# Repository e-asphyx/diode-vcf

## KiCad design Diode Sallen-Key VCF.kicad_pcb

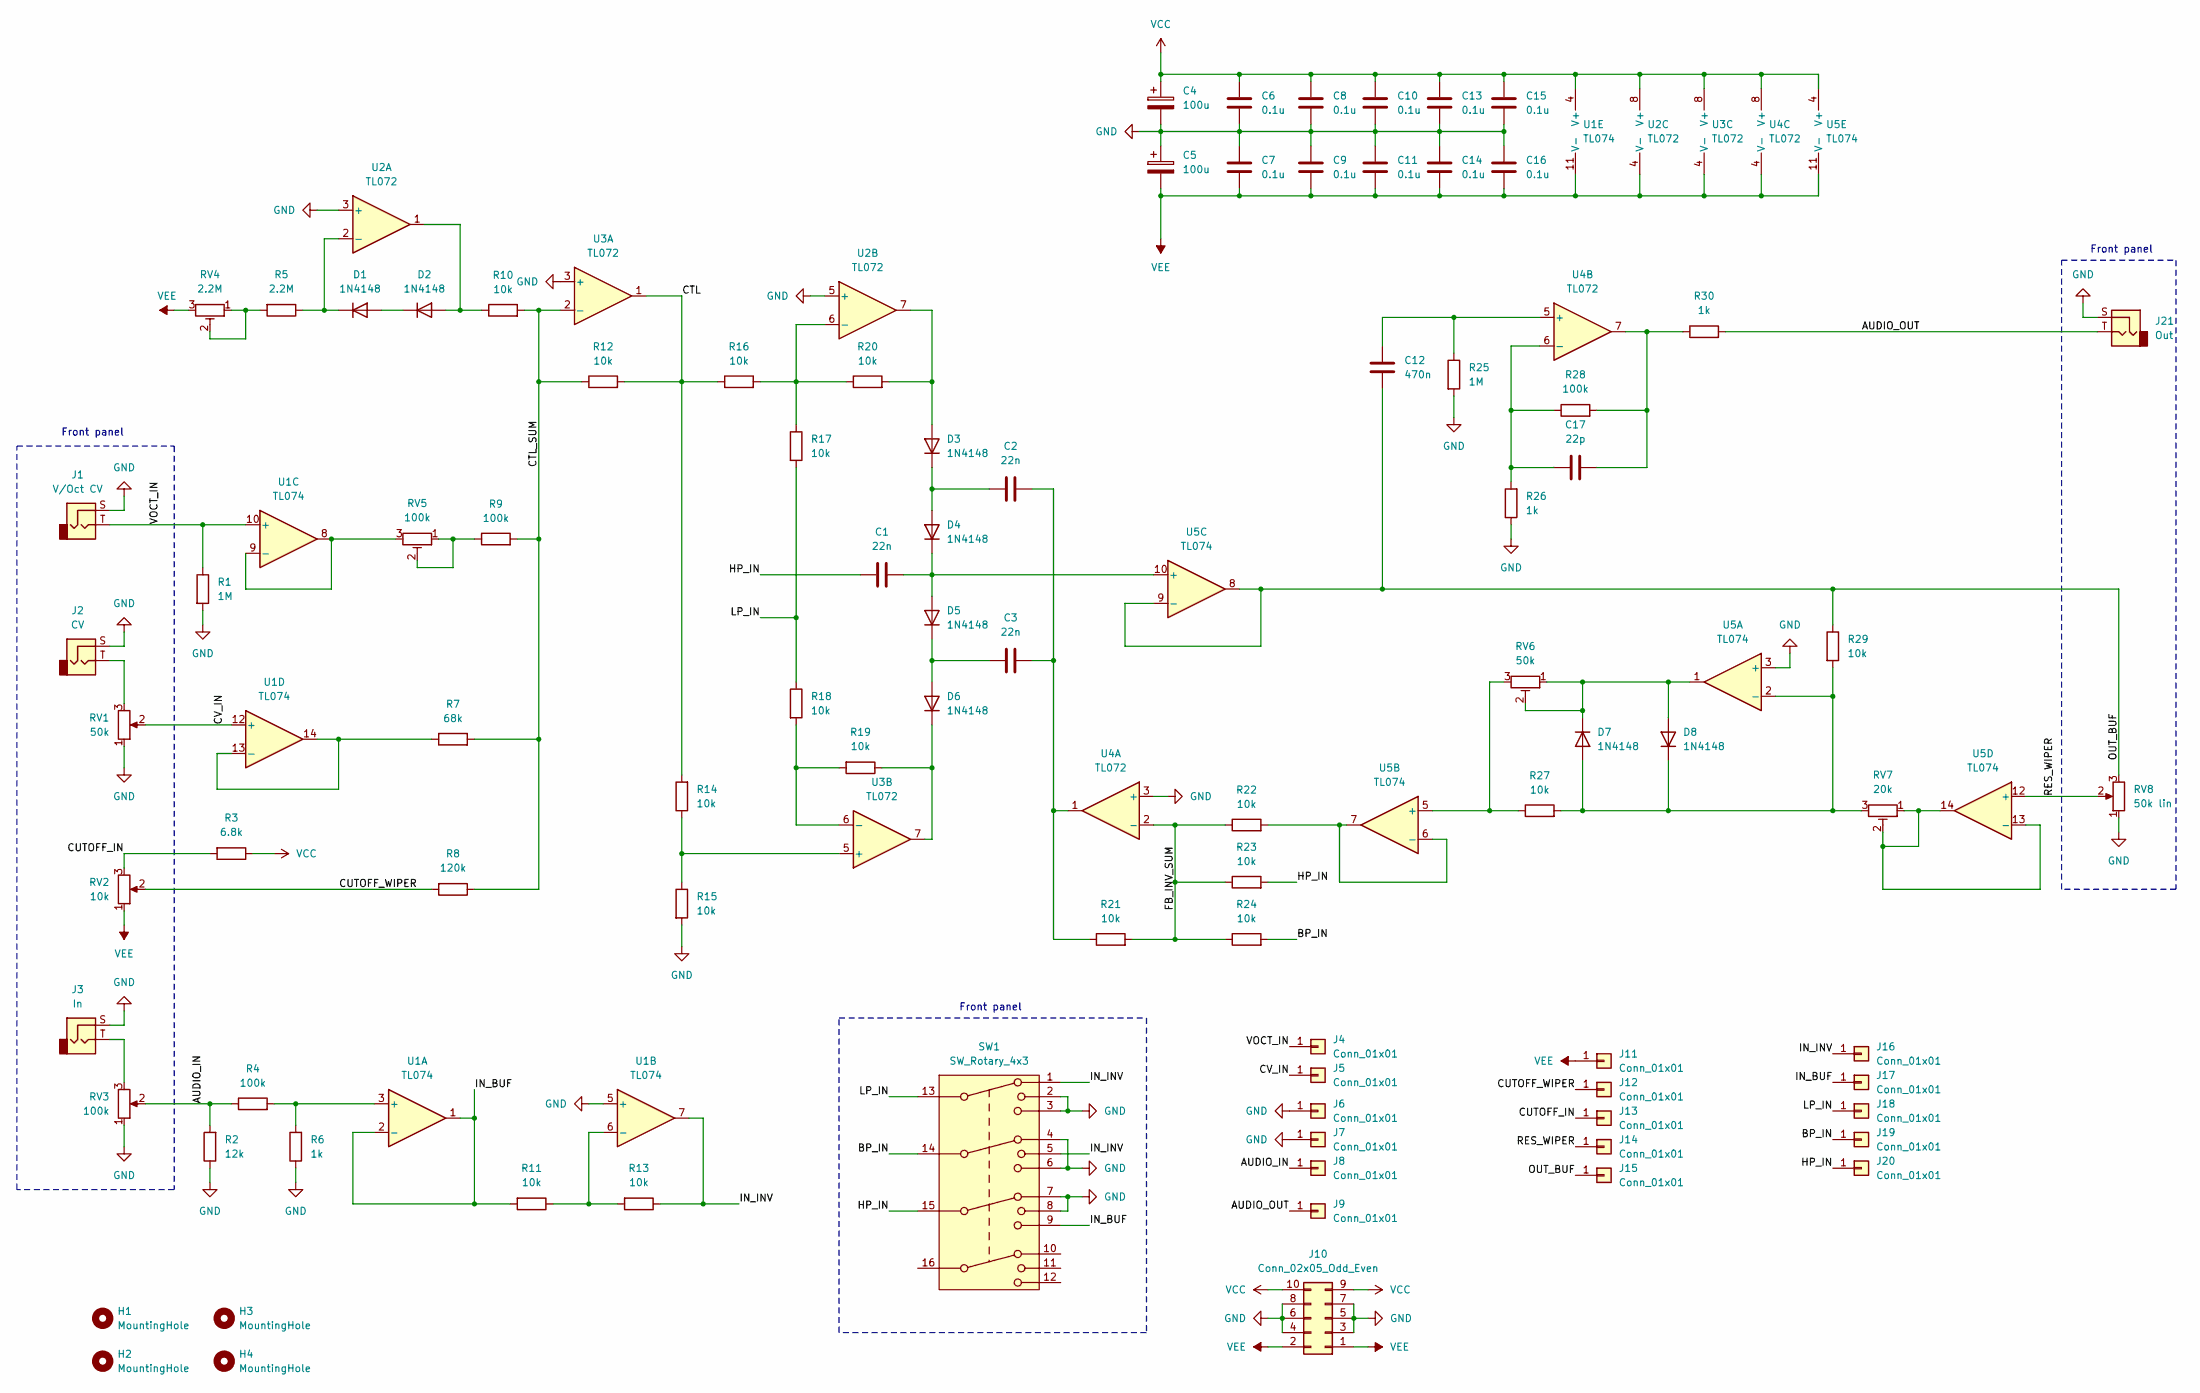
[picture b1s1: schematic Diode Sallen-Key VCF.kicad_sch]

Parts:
C1, C2, C3: 22n; C_Rect_L13.0mm_W4.0mm_P10.00mm_FKS3_FKP3_MKS4
C4, C5: 100u; CP_Radial_D10.0mm_P5.00mm
C6, C7, C8, C9, C10, C11, C13, C14, C15, C16: 0.1u; C_Disc_D5.1mm_W3.2mm_P5.00mm
C12: 470n; C_Rect_L13.0mm_W6.0mm_P10.00mm_FKS3_FKP3_MKS4
C17: 22p; C_Disc_D5.1mm_W3.2mm_P5.00mm
D1, D2, D3, D4, D5, D6, D7, D8: 1N4148; D_DO-35_SOD27_P7.62mm_Horizontal
H1, H2, H3, H4: MountingHole; MountingHole_3.2mm_M3
J1: V/Oct CV
J2: CV
J3: In
J4, J5, J6, J7, J8, J9, J11, J12, J13, J14, J15, J16, J17, J18, J19, J20: Conn_01x01; Pin_D1.3mm_L11.0mm
J10: Conn_02x05_Odd_Even; IDC-Header_2x05_P2.54mm_Vertical
J21: Out
R1, R25: 1M; R_Axial_DIN0207_L6.3mm_D2.5mm_P10.16mm_Horizontal
R2: 12k; R_Axial_DIN0207_L6.3mm_D2.5mm_P10.16mm_Horizontal
R3: 6.8k; R_Axial_DIN0207_L6.3mm_D2.5mm_P10.16mm_Horizontal
R4, R9, R28: 100k; R_Axial_DIN0207_L6.3mm_D2.5mm_P10.16mm_Horizontal
R5: 2.2M; R_Axial_DIN0207_L6.3mm_D2.5mm_P10.16mm_Horizontal
R6, R26, R30: 1k; R_Axial_DIN0207_L6.3mm_D2.5mm_P10.16mm_Horizontal
R7: 68k; R_Axial_DIN0207_L6.3mm_D2.5mm_P10.16mm_Horizontal
R8: 120k; R_Axial_DIN0207_L6.3mm_D2.5mm_P10.16mm_Horizontal
R10, R11, R12, R13, R14, R15, R16, R17, R18, R19, R20, R21, R22, R23, R24, R27, R29: 10k; R_Axial_DIN0207_L6.3mm_D2.5mm_P10.16mm_Horizontal
RV1: 50k
RV2: 10k
RV3: 100k
RV4: 2.2M; Potentiometer_Bourns_3296Y_Vertical
RV5: 100k; Potentiometer_Bourns_3296Y_Vertical
RV6: 50k; Potentiometer_Bourns_3296Y_Vertical
RV7: 20k; Potentiometer_Bourns_3296Y_Vertical
RV8: 50k lin
SW1: SW_Rotary_4x3
U1, U5: TL074; DIP-14_W7.62mm_Socket
U2, U3, U4: TL072; DIP-8_W7.62mm_Socket

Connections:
/AUDIO_IN: J8.1 (Pin_1_1), R2.2, R4.1, RV3.2
/AUDIO_OUT: J9.1 (Pin_1_1), J21.T, R30.2
/BP_IN: J19.1 (Pin_1_1), R24.2, SW1.14
/CTL: R12.2, R14.2, R16.1, U3.1
/CTL_SUM: R7.2, R8.1, R9.2, R10.2, R12.1, U3.2 (-)
/CUTOFF_IN: J13.1 (Pin_1_1), R3.2, RV2.3
/CUTOFF_WIPER: J12.1 (Pin_1_1), R8.2, RV2.2
/CV_IN: J5.1 (Pin_1_1), RV1.2, U1.12 (+)
/FB_INV_SUM: R21.2, R22.1, R23.1, R24.1, U4.2 (-)
/HP_IN: C1.1, J20.1 (Pin_1_1), R23.2, SW1.15
/IN_BUF: J17.1 (Pin_1_1), R11.2, SW1.9, U1.1, U1.2 (-)
/IN_INV: J16.1 (Pin_1_1), R13.1, SW1.1, SW1.5, U1.7
/LP_IN: J18.1 (Pin_1_1), R17.2, R18.1, SW1.13
/OUT_BUF: C12.2, J15.1 (Pin_1_1), R29.1, RV8.3, U5.8, U5.9 (-)
/RES_WIPER: J14.1 (Pin_1_1), RV8.2, U5.12 (+)
/VOCT_IN: J1.T, J4.1 (Pin_1_1), R1.1, U1.10 (+)
GND: C4.2, C5.1, C6.2, C7.1, C8.2, C9.1, C10.2, C11.1, C13.2, C14.1, C15.2, C16.1, J1.S, J2.S, J3.S, J6.1 (Pin_1_1), J7.1 (Pin_1_1), J10.3, J10.4, J10.5, J10.6, J10.7, J10.8, J21.S, R1.2, R2.1, R6.1, R15.2, R25.2, R26.1, RV1.1, RV3.1, RV8.1, SW1.2, SW1.3, SW1.4, SW1.6, SW1.7, SW1.8, U1.5 (+), U2.3 (+), U2.5 (+), U3.3 (+), U4.3 (+), U5.3 (+)
unnamed: C2.2, C3.2, R21.1, U4.1
unnamed: C17.2, R28.2, R30.1, U4.7
unnamed: D1.2 (A), D2.1 (K)
unnamed: D1.1 (K), R5.1, U2.2 (-)
unnamed: D2.2 (A), R10.1, U2.1
unnamed: D3.2 (A), R20.2, U2.7
unnamed: C2.1, D3.1 (K), D4.2 (A)
unnamed: C1.2, D4.1 (K), D5.2 (A), U5.10 (+)
unnamed: C3.1, D5.1 (K), D6.2 (A)
unnamed: D6.1 (K), R19.1, U3.7
unnamed: D7.2 (A), D8.1 (K), R27.2, R29.2, RV7.3, U5.2 (-)
unnamed: D7.1 (K), D8.2 (A), RV6.1, RV6.2, U5.1
unnamed: J2.T, RV1.3
unnamed: J3.T, RV3.3
unnamed: R5.2, RV4.1, RV4.2
unnamed: R9.1, RV5.1, RV5.2
unnamed: R4.2, R6.2, U1.3 (+)
unnamed: R11.1, R13.2, U1.6 (-)
unnamed: RV5.3, U1.8, U1.9 (-)
unnamed: R7.1, U1.13 (-), U1.14
unnamed: R16.2, R17.1, R20.1, U2.6 (-)
unnamed: R14.1, R15.1, U3.5 (+)
unnamed: R18.2, R19.2, U3.6 (-)
unnamed: C12.1, R25.1, U4.5 (+)
unnamed: C17.1, R26.2, R28.1, U4.6 (-)
unnamed: R27.1, RV6.3, U5.5 (+)
unnamed: R22.2, U5.6 (-), U5.7
unnamed: RV7.1, RV7.2, U5.13 (-), U5.14
VCC: C4.1, C6.1, C8.1, C10.1, C13.1, C15.1, J10.9, J10.10, R3.1, U1.4 (V+), U2.8 (V+), U3.8 (V+), U4.8 (V+), U5.4 (V+)
VEE: C5.2, C7.2, C9.2, C11.2, C14.2, C16.2, J10.1, J10.2, J11.1 (Pin_1_1), RV2.1, RV4.3, U1.11 (V-), U2.4 (V-), U3.4 (V-), U4.4 (V-), U5.11 (V-)

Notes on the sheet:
Front panel

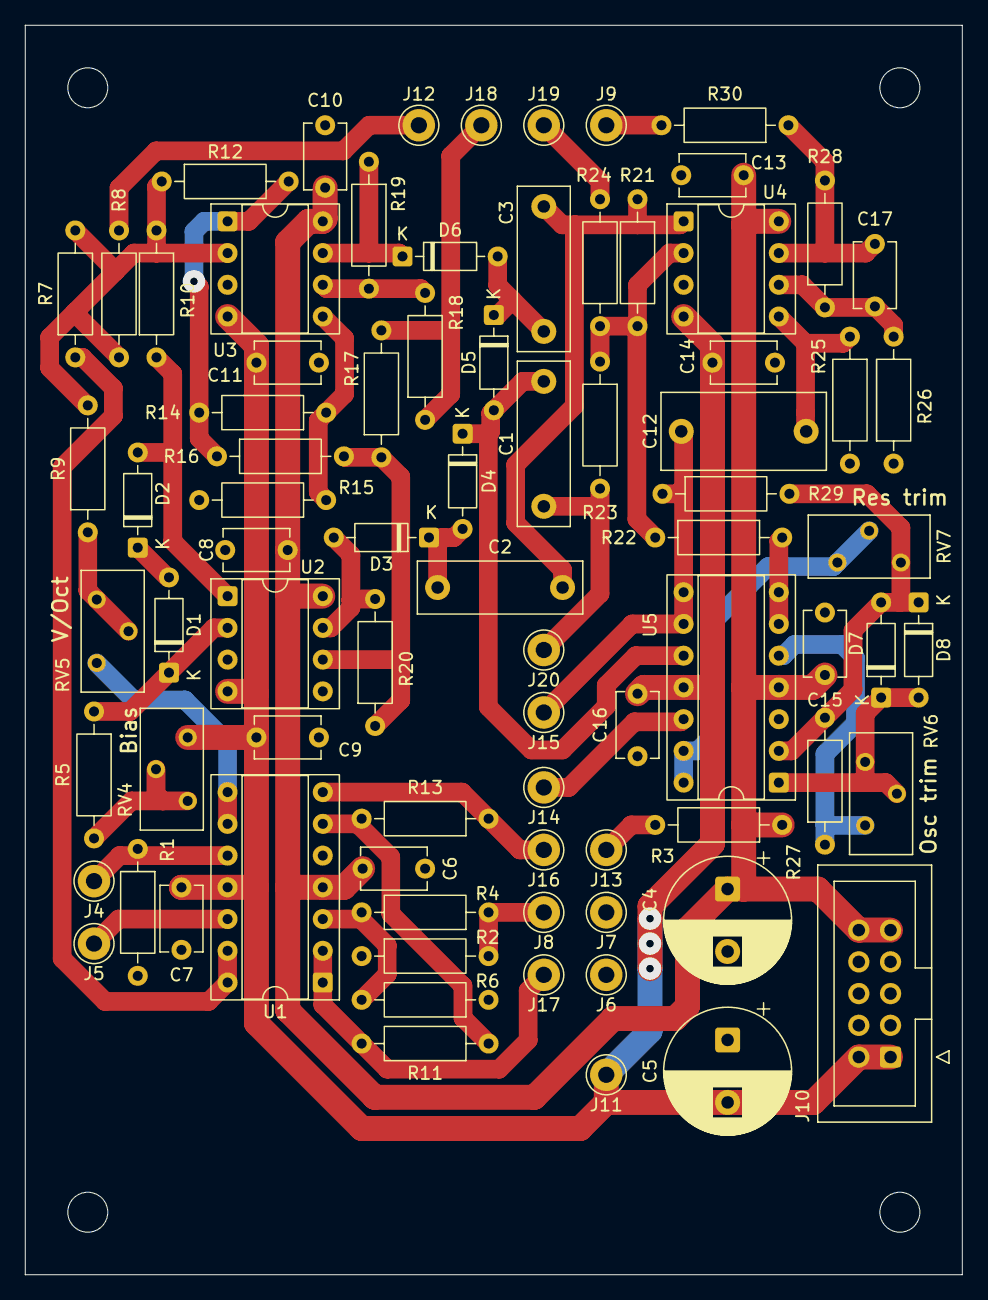
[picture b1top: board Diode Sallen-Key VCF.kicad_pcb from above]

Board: 2 copper layers, 75.0 x 100.0 mm, 85 parts (0 on the bottom side), 45 nets.
